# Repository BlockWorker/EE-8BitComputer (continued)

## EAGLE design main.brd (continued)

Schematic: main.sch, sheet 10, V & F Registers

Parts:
C1000, C1001, C1002, C1003, C1004, C1005: 0.1µF; C0805K
LED1000, LED1001, LED1002, LED1003, LED1004, LED1005, LED1006, LED1007, LED1008, LED1009, LED1010, LED1011, LED1012, LED1013, LED1014, LED1015: red; LED3MM
RN1000, RN1001: 8x220Ω?; CAY16102J8LF
U1000, U1001, U1003, U1004: 74LS173N; DIL16
U1002, U1005: 74LS245N; DIL20

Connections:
!FI: U1003.9 (G1), U1004.9 (G1); also elsewhere on the board
!FO: U1005.19 (G); also elsewhere on the board
!VI: U1000.9 (G1), U1001.9 (G1); also elsewhere on the board
!VO: U1002.19 (G); also elsewhere on the board
CLK: U1000.7 (CLK), U1001.7 (CLK), U1003.7 (CLK), U1004.7 (CLK); also elsewhere on the board
GND: C1000.2, C1001.2, C1002.2, C1003.2, C1004.2, C1005.2, RN1000.9 (R1_2), RN1000.10 (R2_2), RN1000.11 (R3_2), RN1000.12 (R4_2), RN1000.13 (R5_2), RN1000.14 (R6_2), RN1000.15 (R7_2), RN1000.16 (R8_2), RN1001.9 (R1_2), RN1001.10 (R2_2), RN1001.11 (R3_2), RN1001.12 (R4_2), RN1001.13 (R5_2), RN1001.14 (R6_2), RN1001.15 (R7_2), RN1001.16 (R8_2), U1000.1 (M), U1000.2 (N), U1000.8 (GND), U1000.10 (G2), U1001.1 (M), U1001.2 (N), U1001.8 (GND), U1001.10 (G2), U1002.10 (GND), U1003.1 (M), U1003.2 (N), U1003.8 (GND), U1003.10 (G2), U1004.1 (M), U1004.2 (N), U1004.8 (GND), U1004.10 (G2), U1005.10 (GND); also elsewhere on the board
LED1000_GND: LED1000.K (C), RN1000.1 (R1_1)
LED1001_GND: LED1001.K (C), RN1000.2 (R2_1)
LED1002_GND: LED1002.K (C), RN1000.3 (R3_1)
LED1003_GND: LED1003.K (C), RN1000.4 (R4_1)
LED1004_GND: LED1004.K (C), RN1000.8 (R8_1)
LED1005_GND: LED1005.K (C), RN1000.7 (R7_1)
LED1006_GND: LED1006.K (C), RN1000.6 (R6_1)
LED1007_GND: LED1007.K (C), RN1000.5 (R5_1)
LED1008_GND: LED1008.K (C), RN1001.1 (R1_1)
LED1009_GND: LED1009.K (C), RN1001.2 (R2_1)
LED1010_GND: LED1010.K (C), RN1001.3 (R3_1)
LED1011_GND: LED1011.K (C), RN1001.4 (R4_1)
LED1012_GND: LED1012.K (C), RN1001.8 (R8_1)
LED1013_GND: LED1013.K (C), RN1001.7 (R7_1)
LED1014_GND: LED1014.K (C), RN1001.6 (R6_1)
LED1015_GND: LED1015.K (C), RN1001.5 (R5_1)
MAINBUS_0: U1001.11 (D4), U1002.11 (B8), U1004.11 (D4), U1005.11 (B8); also elsewhere on the board
MAINBUS_1: U1001.12 (D3), U1002.12 (B7), U1004.12 (D3), U1005.12 (B7); also elsewhere on the board
MAINBUS_2: U1001.13 (D2), U1002.13 (B6), U1004.13 (D2), U1005.13 (B6); also elsewhere on the board
MAINBUS_3: U1001.14 (D1), U1002.14 (B5), U1004.14 (D1), U1005.14 (B5); also elsewhere on the board
MAINBUS_4: U1000.11 (D4), U1002.15 (B4), U1003.11 (D4), U1005.15 (B4); also elsewhere on the board
MAINBUS_5: U1000.12 (D3), U1002.16 (B3), U1003.12 (D3), U1005.16 (B3); also elsewhere on the board
MAINBUS_6: U1000.13 (D2), U1002.17 (B2), U1003.13 (D2), U1005.17 (B2); also elsewhere on the board
MAINBUS_7: U1000.14 (D1), U1002.18 (B1), U1003.14 (D1), U1005.18 (B1); also elsewhere on the board
REG_F_0: LED1015.A, U1004.6 (Q4), U1005.9 (A8)
REG_F_1: LED1014.A, U1004.5 (Q3), U1005.8 (A7)
REG_F_2: LED1013.A, U1004.4 (Q2), U1005.7 (A6)
REG_F_3: LED1012.A, U1004.3 (Q1), U1005.6 (A5)
REG_F_4: LED1011.A, U1003.6 (Q4), U1005.5 (A4)
REG_F_5: LED1010.A, U1003.5 (Q3), U1005.4 (A3)
REG_F_6: LED1009.A, U1003.4 (Q2), U1005.3 (A2)
REG_F_7: LED1008.A, U1003.3 (Q1), U1005.2 (A1)
REG_V_0: LED1007.A, U1001.6 (Q4), U1002.9 (A8)
REG_V_1: LED1006.A, U1001.5 (Q3), U1002.8 (A7)
REG_V_2: LED1005.A, U1001.4 (Q2), U1002.7 (A6)
REG_V_3: LED1004.A, U1001.3 (Q1), U1002.6 (A5)
REG_V_4: LED1003.A, U1000.6 (Q4), U1002.5 (A4)
REG_V_5: LED1002.A, U1000.5 (Q3), U1002.4 (A3)
REG_V_6: LED1001.A, U1000.4 (Q2), U1002.3 (A2)
REG_V_7: LED1000.A, U1000.3 (Q1), U1002.2 (A1)
RST: U1000.15 (CLR), U1001.15 (CLR), U1003.15 (CLR), U1004.15 (CLR); also elsewhere on the board
VCC: C1000.1, C1001.1, C1002.1, C1003.1, C1004.1, C1005.1, U1000.16 (VCC), U1001.16 (VCC), U1002.1 (DIR), U1002.20 (VCC), U1003.16 (VCC), U1004.16 (VCC), U1005.1 (DIR), U1005.20 (VCC); also elsewhere on the board

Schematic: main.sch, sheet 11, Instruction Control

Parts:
C1100, C1101, C1102, C1103, C1104, C1105, C1106, C1107, C1108, C1109, C1110: 0.1µF; C0805K
LED1100, LED1101, LED1102, LED1103, LED1104, LED1105, LED1106: green; LED3MM
LED1107, LED1108, LED1109, LED1110, LED1111, LED1112, LED1113, LED1114, LED1115, LED1116, LED1117, LED1118: yellow; LED3MM
LED1119, LED1120, LED1121, LED1122, LED1123, LED1124, LED1125, LED1126, LED1127, LED1128, LED1129, LED1130, LED1131, LED1132, LED1133, LED1134, LED1135, LED1136, LED1137, LED1138, LED1139, LED1140, LED1141, LED1142, LED1143, LED1144, LED1145, LED1146, LED1147, LED1148, LED1149, LED1150, LED1151, LED1152, LED1153, LED1154, LED1155, LED1156, LED1157, LED1158, LED1159, LED1160, LED1161, LED1162, LED1163, LED1164: white; LED3MM
R1100, R1101, R1102, R1103: 330Ω?; R0805
RN1100, RN1101, RN1102, RN1103, RN1104, RN1105, RN1106, RN1107: 8x220Ω?; CAY16102J8LF
U800, U1108: 74LS04N; DIL14
U1100, U1101: 74LS173N; DIL16
U1102: 74LS161N; DIL16
U1106, U1107: 74HCT154DW; SO24W
XU1103, XU1104, XU1105: AT28C64B; DIL28

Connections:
!AI: LED1119.K (C), U1106.2 (1); also elsewhere on the board
!AO: LED1134.K (C), U1107.2 (1); also elsewhere on the board
!BI: LED1120.K (C), U1106.3 (2); also elsewhere on the board
!CI: LED1121.K (C), U1106.4 (3); also elsewhere on the board
!CLK: U800.12 (O), U1102.2 (CLK)
!CMP: U800.2 (O); also elsewhere on the board
!CMPO: LED1136.K (C), U1107.4 (3); also elsewhere on the board
!CO: LED1135.K (C), U1107.3 (2); also elsewhere on the board
!EO: LED1137.K (C), U1107.5 (4); also elsewhere on the board
!FE: U1108.10 (O); also elsewhere on the board
!FI: LED1122.K (C), U1106.5 (4); also elsewhere on the board
!FO: LED1138.K (C), U1107.6 (5); also elsewhere on the board
!II: LED1123.K (C), U1100.9 (G1), U1101.9 (G1), U1106.6 (5)
!MHI: LED1124.K (C), U1106.7 (6); also elsewhere on the board
!MLI: LED1125.K (C), U1106.8 (7); also elsewhere on the board
!NO: LED1139.K (C), U1107.7 (6); also elsewhere on the board
!OI: LED1126.K (C), U1106.9 (8); also elsewhere on the board
!OMI: LED1127.K (C), U1106.10 (9); also elsewhere on the board
!OO: LED1140.K (C), U1107.8 (7); also elsewhere on the board
!OUT_15: LED1148.K (C), U1107.17 (15)
!PI: LED1128.K (C), U1106.11 (10); also elsewhere on the board
!PO: LED1141.K (C), U1107.9 (8); also elsewhere on the board
!RI: LED1129.K (C), U1106.13 (11), U1108.1 (I)
!RM: U1108.6 (O); also elsewhere on the board
!RMSB: U1108.8 (O); also elsewhere on the board
!RM_INT: U1102.1 (CLR); also elsewhere on the board
!RO: LED1142.K (C), U1107.10 (9), U1108.13 (I)
!SO: LED1143.K (C), U1107.11 (10); also elsewhere on the board
!TO: LED1144.K (C), U1107.13 (11); also elsewhere on the board
!VI: LED1130.K (C), U1106.14 (12); also elsewhere on the board
!VO: LED1145.K (C), U1107.14 (12); also elsewhere on the board
!XI: LED1131.K (C), U1106.15 (13), U1108.3 (I)
!ZHI: LED1132.K (C), U1106.16 (14); also elsewhere on the board
!ZHO: LED1146.K (C), U1107.15 (13); also elsewhere on the board
!ZLI: LED1133.K (C), U1106.17 (15); also elsewhere on the board
!ZLO: LED1147.K (C), U1107.16 (14); also elsewhere on the board
ANY_INPUT: U1106.1 (0); also elsewhere on the board
CE: LED1149.A, XU1104.11 (D0); also elsewhere on the board
CLK: U800.13 (I), U1100.7 (CLK), U1101.7 (CLK); also elsewhere on the board
CMP: LED1150.A, U800.1 (I), XU1104.12 (D1)
CPB0: LED1151.A, XU1104.13 (D2); also elsewhere on the board
CPB1: LED1152.A, XU1104.15 (D3); also elsewhere on the board
CPTC: LED1153.A, XU1104.16 (D4); also elsewhere on the board
FE: LED1154.A, U1108.11 (I), XU1104.17 (D5)
GND: C1100.2, C1101.2, C1102.2, C1103.2, C1104.2, C1105.2, C1106.2, C1107.2, C1108.2, C1109.2, C1110.2, R1100.2, R1101.2, R1102.2, R1103.2, RN1100.9 (R1_2), RN1100.10 (R2_2), RN1100.11 (R3_2), RN1100.12 (R4_2), RN1100.13 (R5_2), RN1100.14 (R6_2), RN1100.15 (R7_2), RN1100.16 (R8_2), RN1101.9 (R1_2), RN1101.10 (R2_2), RN1101.11 (R3_2), RN1101.12 (R4_2), RN1101.13 (R5_2), RN1101.14 (R6_2), RN1101.15 (R7_2), RN1101.16 (R8_2), RN1106.9 (R1_2), RN1106.10 (R2_2), RN1106.11 (R3_2), RN1106.12 (R4_2), RN1106.13 (R5_2), RN1106.14 (R6_2), RN1106.15 (R7_2), RN1106.16 (R8_2), RN1107.9 (R1_2), RN1107.10 (R2_2), RN1107.11 (R3_2), RN1107.12 (R4_2), RN1107.13 (R5_2), RN1107.14 (R6_2), RN1107.15 (R7_2), RN1107.16 (R8_2), U800.7 (GND), U1100.1 (M), U1100.2 (N), U1100.8 (GND), U1100.10 (G2), U1101.1 (M), U1101.2 (N), U1101.8 (GND), U1101.10 (G2), U1101.11 (D4), U1102.8 (GND), U1106.12 (GND), U1106.18 (G1), U1106.19 (G2), U1107.12 (GND), U1107.18 (G1), U1107.19 (G2), U1108.7 (GND), XU1103.14 (GND), XU1103.20 (!CE), XU1103.22 (!OE), XU1104.14 (GND), XU1104.20 (!CE), XU1104.22 (!OE), XU1105.14 (GND), XU1105.20 (!CE), XU1105.22 (!OE); also elsewhere on the board
GT: XU1103.2 (A12), XU1104.2 (A12), XU1105.2 (A12); also elsewhere on the board
HLT: LED1155.A, XU1104.18 (D6); also elsewhere on the board
INT_INSTR_I_0: LED1106.A, U1100.3 (Q1), XU1103.6 (A4), XU1104.6 (A4), XU1105.6 (A4)
INT_INSTR_I_1: LED1105.A, U1100.4 (Q2), XU1103.5 (A5), XU1104.5 (A5), XU1105.5 (A5)
INT_INSTR_I_2: LED1104.A, U1100.5 (Q3), XU1103.4 (A6), XU1104.4 (A6), XU1105.4 (A6)
INT_INSTR_I_3: LED1103.A, U1100.6 (Q4), XU1103.3 (A7), XU1104.3 (A7), XU1105.3 (A7)
INT_INSTR_I_4: LED1102.A, U1101.3 (Q1), XU1103.25 (A8), XU1104.25 (A8), XU1105.25 (A8)
INT_INSTR_I_5: LED1101.A, U1101.4 (Q2), XU1103.24 (A9), XU1104.24 (A9), XU1105.24 (A9)
INT_INSTR_I_6: LED1100.A, U1101.5 (Q3), XU1103.21 (A10), XU1104.21 (A10), XU1105.21 (A10)
INT_INSTR_M_0: LED1110.A, U1102.14 (QA), XU1103.10 (A0), XU1104.10 (A0), XU1105.10 (A0)
INT_INSTR_M_1: LED1109.A, U1102.13 (QB), XU1103.9 (A1), XU1104.9 (A1), XU1105.9 (A1)
INT_INSTR_M_2: LED1108.A, U1102.12 (QC), XU1103.8 (A2), XU1104.8 (A2), XU1105.8 (A2)
INT_INSTR_M_3: LED1107.A, U1102.11 (QD), XU1103.7 (A3), XU1104.7 (A3), XU1105.7 (A3)
IN_INDEX_0: LED1118.A, U1106.23 (A), XU1103.11 (D0)
IN_INDEX_1: LED1117.A, U1106.22 (B), XU1103.12 (D1)
IN_INDEX_2: LED1116.A, U1106.21 (C), XU1103.13 (D2)
IN_INDEX_3: LED1115.A, U1106.20 (D), XU1103.15 (D3)
LED1100_GND: LED1100.K (C), RN1100.1 (R1_1)
LED1101_GND: LED1101.K (C), RN1100.2 (R2_1)
LED1102_GND: LED1102.K (C), RN1100.3 (R3_1)
LED1103_GND: LED1103.K (C), RN1100.4 (R4_1)
LED1104_GND: LED1104.K (C), RN1100.5 (R5_1)
LED1105_GND: LED1105.K (C), RN1100.6 (R6_1)
LED1106_GND: LED1106.K (C), RN1100.7 (R7_1)
LED1107_GND: LED1107.K (C), R1100.1
LED1108_GND: LED1108.K (C), R1101.1
LED1109_GND: LED1109.K (C), R1102.1
LED1110_GND: LED1110.K (C), R1103.1
LED1111_GND: LED1111.K (C), RN1101.8 (R8_1)
LED1112_GND: LED1112.K (C), RN1101.7 (R7_1)
LED1113_GND: LED1113.K (C), RN1101.6 (R6_1)
LED1114_GND: LED1114.K (C), RN1101.5 (R5_1)
LED1115_GND: LED1115.K (C), RN1101.4 (R4_1)
LED1116_GND: LED1116.K (C), RN1101.3 (R3_1)
LED1117_GND: LED1117.K (C), RN1101.2 (R2_1)
LED1118_GND: LED1118.K (C), RN1101.1 (R1_1)
LED1119_VCC: LED1119.A, RN1102.2 (R2_1)
LED1120_VCC: LED1120.A, RN1102.3 (R3_1)
LED1121_VCC: LED1121.A, RN1102.4 (R4_1)
LED1122_VCC: LED1122.A, RN1102.5 (R5_1)
LED1123_VCC: LED1123.A, RN1102.6 (R6_1)
LED1124_VCC: LED1124.A, RN1102.7 (R7_1)
LED1125_VCC: LED1125.A, RN1102.8 (R8_1)
LED1126_VCC: LED1126.A, RN1103.1 (R1_1)
LED1127_VCC: LED1127.A, RN1103.2 (R2_1)
LED1128_VCC: LED1128.A, RN1103.3 (R3_1)
LED1129_VCC: LED1129.A, RN1103.4 (R4_1)
LED1130_VCC: LED1130.A, RN1103.5 (R5_1)
LED1131_VCC: LED1131.A, RN1103.6 (R6_1)
LED1132_VCC: LED1132.A, RN1103.7 (R7_1)
LED1133_VCC: LED1133.A, RN1103.8 (R8_1)
LED1134_VCC: LED1134.A, RN1104.7 (R7_1)
LED1135_VCC: LED1135.A, RN1104.6 (R6_1)
LED1136_VCC: LED1136.A, RN1104.5 (R5_1)
LED1137_VCC: LED1137.A, RN1104.4 (R4_1)
LED1138_VCC: LED1138.A, RN1104.3 (R3_1)
LED1139_VCC: LED1139.A, RN1104.2 (R2_1)
LED1140_VCC: LED1140.A, RN1104.1 (R1_1)
LED1141_VCC: LED1141.A, RN1105.8 (R8_1)
LED1142_VCC: LED1142.A, RN1105.7 (R7_1)
LED1143_VCC: LED1143.A, RN1105.6 (R6_1)
LED1144_VCC: LED1144.A, RN1105.5 (R5_1)
LED1145_VCC: LED1145.A, RN1105.4 (R4_1)
LED1146_VCC: LED1146.A, RN1105.3 (R3_1)
LED1147_VCC: LED1147.A, RN1105.2 (R2_1)
LED1148_VCC: LED1148.A, RN1105.1 (R1_1)
LED1149_GND: LED1149.K (C), RN1106.8 (R8_1)
LED1150_GND: LED1150.K (C), RN1106.7 (R7_1)
LED1151_GND: LED1151.K (C), RN1106.6 (R6_1)
LED1152_GND: LED1152.K (C), RN1106.5 (R5_1)
LED1153_GND: LED1153.K (C), RN1106.4 (R4_1)
LED1154_GND: LED1154.K (C), RN1106.3 (R3_1)
LED1155_GND: LED1155.K (C), RN1106.2 (R2_1)
LED1156_GND: LED1156.K (C), RN1106.1 (R1_1)
LED1157_GND: LED1157.K (C), RN1107.8 (R8_1)
LED1158_GND: LED1158.K (C), RN1107.7 (R7_1)
LED1159_GND: LED1159.K (C), RN1107.6 (R6_1)
LED1160_GND: LED1160.K (C), RN1107.5 (R5_1)
LED1161_GND: LED1161.K (C), RN1107.4 (R4_1)
LED1162_GND: LED1162.K (C), RN1107.3 (R3_1)
LED1163_GND: LED1163.K (C), RN1107.2 (R2_1)
LED1164_GND: LED1164.K (C), RN1107.1 (R1_1)
LT: XU1103.23 (A11), XU1104.23 (A11), XU1105.23 (A11); also elsewhere on the board
MAINBUS_0: U1100.14 (D1); also elsewhere on the board
MAINBUS_1: U1100.13 (D2); also elsewhere on the board
MAINBUS_2: U1100.12 (D3); also elsewhere on the board
MAINBUS_3: U1100.11 (D4); also elsewhere on the board
MAINBUS_4: U1101.14 (D1); also elsewhere on the board
MAINBUS_5: U1101.13 (D2); also elsewhere on the board
MAINBUS_6: U1101.12 (D3); also elsewhere on the board
OUT_INDEX_0: LED1114.A, U1107.23 (A), XU1103.16 (D4)
OUT_INDEX_1: LED1113.A, U1107.22 (B), XU1103.17 (D5)
OUT_INDEX_2: LED1112.A, U1107.21 (C), XU1103.18 (D6)
OUT_INDEX_3: LED1111.A, U1107.20 (D), XU1103.19 (D7)
RI: U1108.2 (O); also elsewhere on the board
RM: C1109.1, LED1156.A, U1108.5 (I), XU1104.19 (D7)
RMSB: C1110.1, LED1157.A, U1108.9 (I), XU1105.11 (D0)
RO: U1108.12 (O); also elsewhere on the board
RST: U1100.15 (CLR), U1101.15 (CLR); also elsewhere on the board
SM0: LED1158.A, XU1105.12 (D1); also elsewhere on the board
SM1: LED1159.A, XU1105.13 (D2); also elsewhere on the board
SRO: LED1160.A, XU1105.15 (D3); also elsewhere on the board
SUB: LED1161.A, XU1105.16 (D4); also elsewhere on the board
T0: LED1162.A, XU1105.17 (D5); also elsewhere on the board
T1: LED1163.A, XU1105.18 (D6); also elsewhere on the board
VCC: C1100.1, C1101.1, C1102.1, C1103.1, C1104.1, C1105.1, C1106.1, C1107.1, C1108.1, RN1102.9 (R1_2), RN1102.10 (R2_2), RN1102.11 (R3_2), RN1102.12 (R4_2), RN1102.13 (R5_2), RN1102.14 (R6_2), RN1102.15 (R7_2), RN1102.16 (R8_2), RN1103.9 (R1_2), RN1103.10 (R2_2), RN1103.11 (R3_2), RN1103.12 (R4_2), RN1103.13 (R5_2), RN1103.14 (R6_2), RN1103.15 (R7_2), RN1103.16 (R8_2), RN1104.9 (R1_2), RN1104.10 (R2_2), RN1104.11 (R3_2), RN1104.12 (R4_2), RN1104.13 (R5_2), RN1104.14 (R6_2), RN1104.15 (R7_2), RN1104.16 (R8_2), RN1105.9 (R1_2), RN1105.10 (R2_2), RN1105.11 (R3_2), RN1105.12 (R4_2), RN1105.13 (R5_2), RN1105.14 (R6_2), RN1105.15 (R7_2), RN1105.16 (R8_2), U800.14 (VCC), U1100.16 (VCC), U1101.16 (VCC), U1102.3 (A), U1102.4 (B), U1102.5 (C), U1102.6 (D), U1102.7 (ENP), U1102.9 (LD), U1102.10 (ENT), U1102.16 (VCC), U1106.24 (VCC), U1107.24 (VCC), U1108.14 (VCC), XU1103.27 (!WE), XU1103.28 (VCC), XU1104.27 (!WE), XU1104.28 (VCC), XU1105.27 (!WE), XU1105.28 (VCC); also elsewhere on the board
XI: U1108.4 (O); also elsewhere on the board
XR: LED1164.A, XU1105.19 (D7); also elsewhere on the board

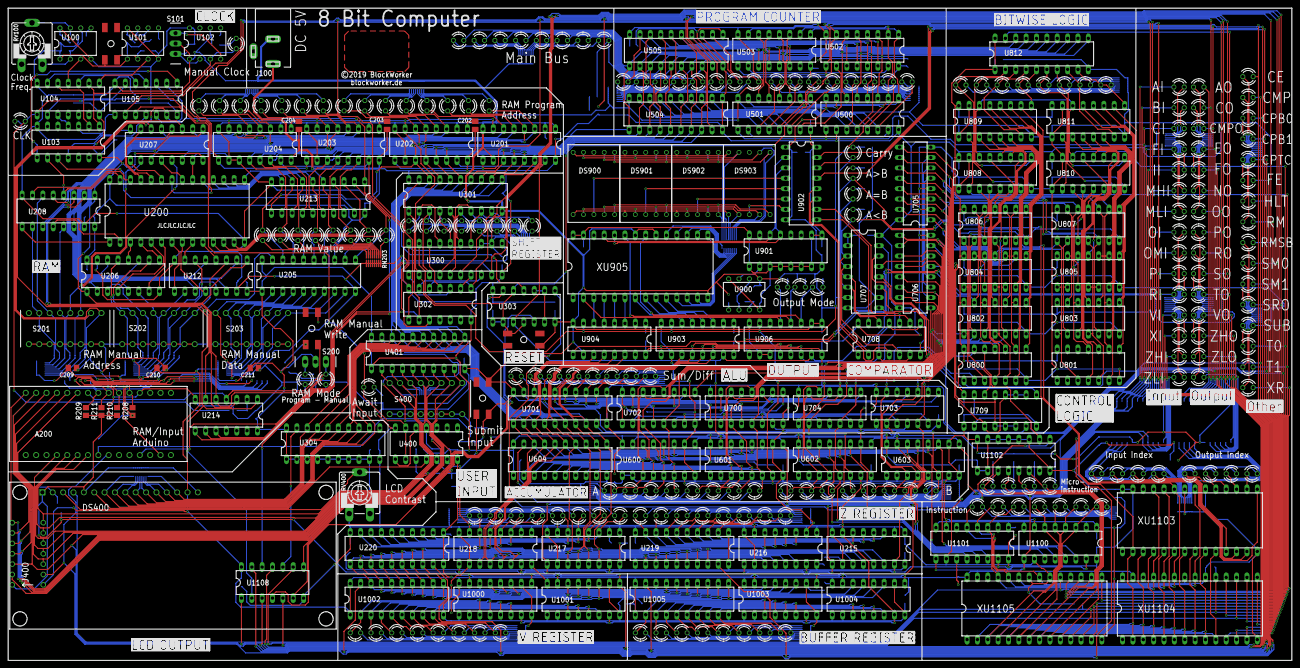
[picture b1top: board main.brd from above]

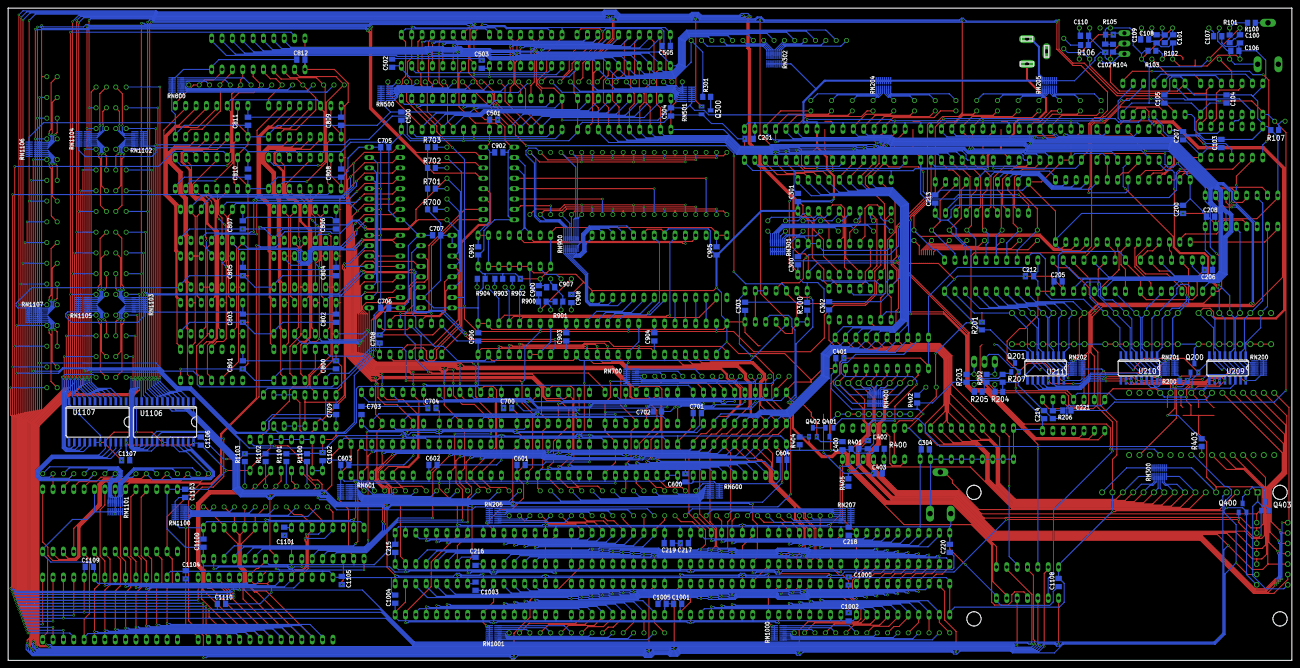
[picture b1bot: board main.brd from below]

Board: 2 copper layers, 314.5 x 159.8 mm, 485 parts (173 on the bottom side), 600 nets.

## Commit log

2019-04-10 Moved ResNet to included library.
2019-04-11 Some work on OUT module.
2019-04-24 Finished OUT module.
2019-04-24 CMP Beginnings
2019-04-24 Arranged modules, some bus connections.
2019-04-24 Most inter-module connections done, added RESET.
2019-04-24 Eagle 9.4.0 update.
2019-04-25 Z register mostly done.
2019-04-26 Finished Z, V and F registers.
2019-04-26 Cleanup and routing of all non-CTRL signals.
2019-05-05 Routing and layout done.
2019-05-05 Revised external input, progress on silkscreen.
2019-05-05 Progress on silkscreen.
2019-05-05 NegaSilk labels added.
2019-05-06 Final design with gerber files.
2019-10-09 Fixed issues encountered during build and testing.
2019-10-09 Moved library over to central BW lib, added gitignore
2019-10-09 Remove eagle backup files.
